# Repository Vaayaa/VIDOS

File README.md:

# VIDOS: Shader Based Video Synthesizer

## Overview

The VIDOS is a flexible Raspberry Pi based video synthesizer with OSC & CV inputs. At its core the device is built around shaders (video card code) and uses them to generate the visuals. VIDOS is a great way to interface the world of shader visuals with analog CV equipment such as Eurorack synthesizers or anything that happens to speak OSC.

Turn the knobs and explore or plug in your eurorack to create your own audio/visual universe!

Features:
- Runs on a Pi Zero
- Bipolar -5V to +5V CV inputs (Eurorack friendly!)
- Instantly Updating Shader Code (Live Coding Encouraged)
- OSC support
	- SHAPEFINDER Layout for Lemur & TouchOSC
- Open Source

Future Features:
- A Shader Specialized Eurorack Module
- MIDI Support

## OSC Control
Do you have one of those addicting pocket thingies?! Send packets with an app like TouchOSC or Lemur and control that shader! Send stuff to /vidos/0 ... 7 to control the corresponding CVs in the .frag

You can find Layouts in the /OSCLayouts Folder

## SHAPEFINDER 
The VIDOS comes with the SHAPEFINDER shader and Layout as a starting point for your own creations

This shader should start automatically when you run the main.out

## Writing Your Own Shaders

VIDOS is basically just a Raspberry Pi in a convenient package that is ready to be programmed.

### OVER WIFI using Sublime Text editor
1. Get Sublime here: https://www.sublimetext.com/
2. Use Sublime's SFTP package: https://wbond.net/sublime_packages/sftp
3. Follow the directions to edit /VIDOS/MyShader0.frag

## Learning About Shaders
Sound intimidating? It isn't! Shader Language is only slightly different from regular C based coding and is super fun!

Check out: https://thebookofshaders.com/ and you will be creating your own craziness in a matter of minutes.

When you're ready to take the show on the road and/or open your creations up to the world of modular synthesizers, take that same code and plug it into the VIDOS.

## Hardware CV Control
The hardware device comes with bipolar CV inputs that can be used to control each of these knobs with voltage rather than turning them by hand. When an input is present the position of the knob represents the center or 0V state of the parameter.

Pair VIDOS with an external LFO for slow morphing changes or patch in your modular sequencer for rhythmic frames in sync with the rest of your patch.

# Installation
## Software
0. flash rasbian
8. git clone https://github.com/teafella/VIDOS
59. ./install.sh

## Controlling the Shader (OSC SETUP)
1. Make sure your phone/pi are connected to thesame wifi network
2. Open A Lemur/TouchOSC layout on your phone
3. Point Lemur/TouchOSC at the pi (raspberrypi.local @ port 7000)

# OPTIONAL Setup
### Optional Installation (You probably already have this in default rasbian)
5. install wiringPI: http://wiringpi.com/download-and-install/

## Creating a Headless Raspberry Pi Zero (Ez Dev Ready Rig)

### Gear
- Pi Zero
- Micro USB cable
- Yurr Laptop

### Steps
1. OTG that thang:
		Guide: https://gist.github.com/gbaman/975e2db164b3ca2b51ae11e45e8fd40a 
2. Make sure you are sharing your wifi Connection: 
		OSX Guide: https://stevegrunwell.com/blog/raspberry-pi-zero-share-internet/
3. Log in with VNC: 
		Instructions: https://raspberrypi.stackexchange.com/questions/13986/how-to-have-remote-desktop-on-macbook-with-raspberry-pi

# Hardware (Dev Notes)

### MCP3008 Pinout

## About The Creator
Ronald Sardarian is a musician, creative programmer and modular synthesizer enthusiast.

Check out [sardarian.wordpress.com](sardarian.wordpress.com) for more projects and [instagram.com/teafela/](instagram.com/teafela) for electronic music and visuals.

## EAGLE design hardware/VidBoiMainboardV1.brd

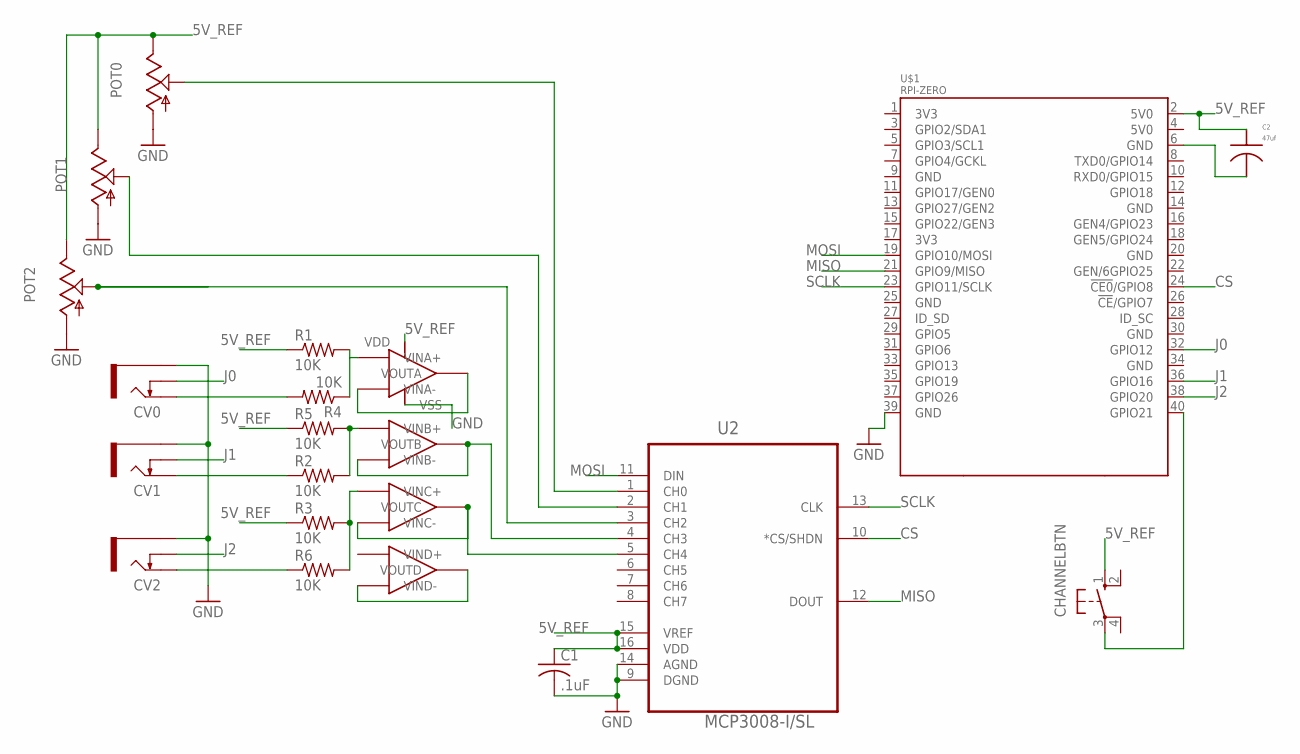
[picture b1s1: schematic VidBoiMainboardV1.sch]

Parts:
C1: .1uF; C025-024X044
C2: 47uf; CAP-PAN-FKS_V-DIM_C
CHANNELBTN: 10-XX; B3F-10XX
CV0, CV1, CV2: THONKICONNOLD; THONKICONN
POT0, POT1, POT2: 9MM_SNAP-IN_POT_; 9MM_SNAP-IN_POT
R1, R2, R3, R4, R5, R6: 10K; R0603
U2: MCP3008-I/SL; SOIC127P600X175-16N
U$1: RPI-ZERO; RASPBERRYPI_BASTELSTUBE_V13_RASPI_BOARD_B+_FULL
U$2: MCP6004SOIC-14; MCP6004ISL

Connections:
5V_REF: C1.1, C2.POS, CHANNELBTN.1 (S), POT0.3 (E), POT1.3 (E), POT2.3 (E), R1.1, R3.1, R5.1, U2.15 (VREF), U2.16 (VDD), U$1.2 (5V0), U$2.VDD
CS: U2.10 (*CS/SHDN), U$1.24 (!CE0!/GPIO8)
GND: C1.2, CV0.P$1_SLEEVE (SLEEVE), CV1.P$1_SLEEVE (SLEEVE), CV2.P$1_SLEEVE (SLEEVE), POT0.1 (A), POT1.1 (A), POT2.1 (A), U2.9 (DGND), U2.14 (AGND), U$1.39 (GND), U$2.VSS
GND@8: C2.NEG, U$1.6 (GND)
J0: CV0.P$2_SWITCH (SWITCH), U$1.32 (GPIO12)
J1: CV1.P$2_SWITCH (SWITCH), U$1.36 (GPIO16)
J2: CV2.P$2_SWITCH (SWITCH), U$1.38 (GPIO20)
MISO: U2.12 (DOUT), U$1.21 (GPIO9/MISO)
MOSI: U2.11 (DIN), U$1.19 (GPIO10/MOSI)
unnamed: CV0.P$3_TIP (TIP), R4.2
unnamed: R1.2, R4.1, U$2.VINA+
unnamed: CV1.P$3_TIP (TIP), R2.1
unnamed: U$2.VINA-, U$2.VOUTA
unnamed: POT0.2 (S), U2.1 (CH0)
unnamed: POT1.2 (S), U2.2 (CH1)
unnamed: POT2.2 (S), U2.3 (CH2)
unnamed: U2.4 (CH3), U$2.VINB-, U$2.VOUTB
unnamed: R3.2, R6.2, U$2.VINC+
unnamed: U2.5 (CH4), U$2.VINC-, U$2.VOUTC
unnamed: U$2.VIND-, U$2.VOUTD
unnamed: CV2.P$3_TIP (TIP), R6.1
unnamed: R2.2, R5.2, U$2.VINB+
unnamed: CHANNELBTN.3, U$1.40 (GPIO21)
SCLK: U2.13 (CLK), U$1.23 (GPIO11/SCLK)

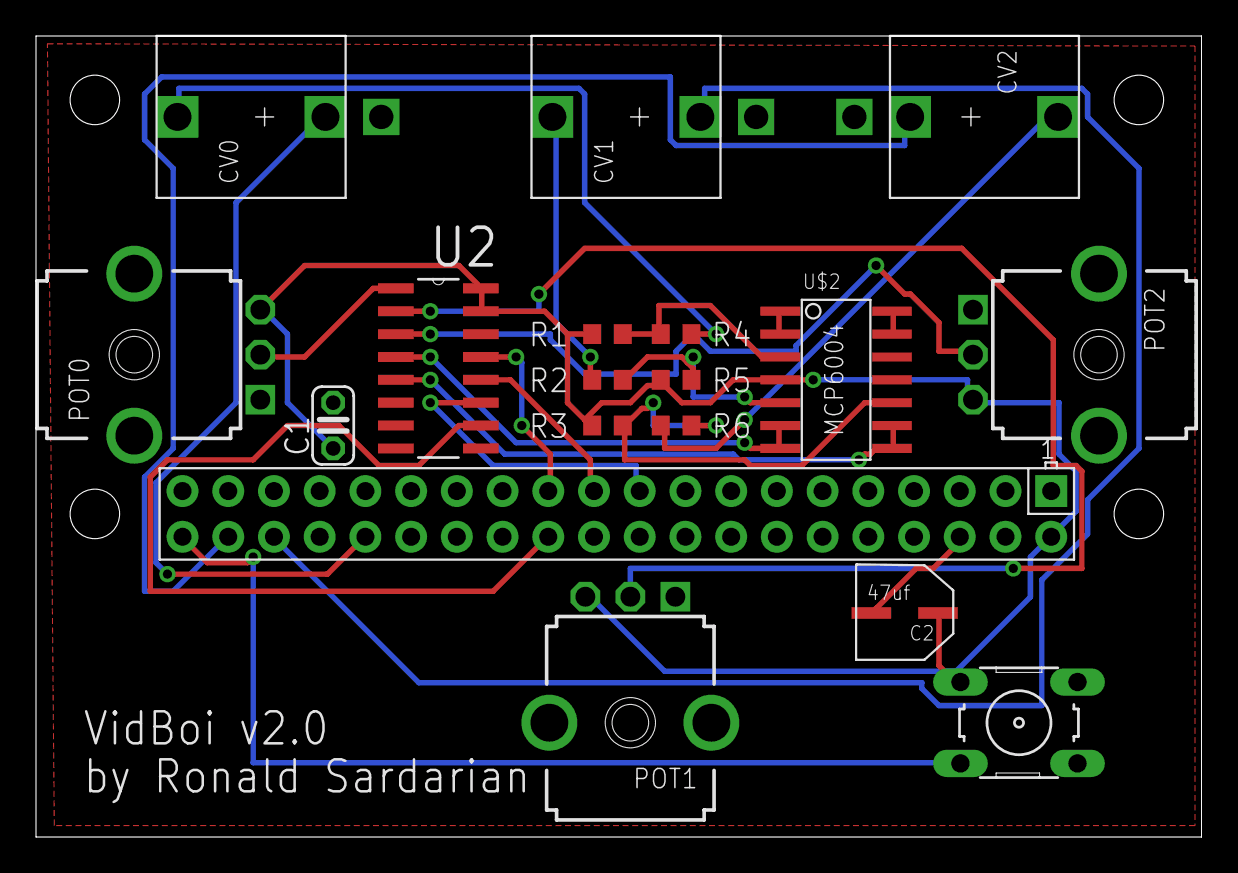
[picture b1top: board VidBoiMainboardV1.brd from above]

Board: 2 copper layers, 64.8 x 44.5 mm, 18 parts (0 on the bottom side), 24 nets.

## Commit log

2018-05-02 Update README.md
    Note about wiring PI installation
2018-05-25 Started re-thinking CV input for V
2018-06-09 Recovered/Correct CV arrays
2018-06-09 Added V1 Board/Schematic
2018-06-09 File Organization
2018-06-09 Added refrence schematic for DAC
2018-06-10 1 Pot Colorizer/Kluer
2018-06-19 Optimization tests
2018-06-19 Added audio libs and build flags
2018-08-02 Audio oscs
2018-08-03 Umm, visuals?
2018-08-04 Pitch controlls / Basic FM OSCs
2018-08-07 Automatic Shader Recompilation On Edit!
2018-08-10 Smoothing inputs
2018-10-26 Changes?
2018-10-27 OSC Control!
2018-10-27 Merging OSC
2018-10-27 Merging OSC Bugfixing :/
2018-10-29 feedback/SD context/fixed switches vidos/100+ are switch controlls
2018-10-29 Shader explorations
2018-11-21 Removed unused osc file
2018-11-21 Moving oscpack library
2018-11-21 added proper oscpack submodule
2018-11-22 added osc so
2018-12-10 VIDOS Readme and Organization
2018-12-10 Readme update
2018-12-14 Installation script
2018-12-21 install scripts tweaks
2018-12-22 Multiplexed Pots
2018-12-23 More datasheets
2018-12-23 readme?
2018-12-24 install script bugs
